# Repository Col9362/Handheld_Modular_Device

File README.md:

# Handheld Modular Device

A handheld built around hot-swappable control modules. Modules attach to the base unit
through an 8-pin pogo connector, and the base detects which module is attached
over I2C plus a resistor-divider ID line.

More details and photos: https://colezuckerman.com/projects/modular-handheld/

## Repository layout

| Folder | Contents |
|---|---|
| `base/` | KiCad project for the base unit (Raspberry Pi Pico, display connector, buzzers, pogo connector) |
| `base/gerbers/` | Manufacturing files for the base unit PCB |
| `base/backup-2026-06-27/` | Earlier snapshot of the base unit KiCad project |
| `gaming-module/` | Gaming controller module (MCP23017 buttons, joystick, haptics) |
| `gaming-module/gerbers/` | Manufacturing files for the gaming module PCB |
| `firmware/` | MicroPython code that runs on the base unit's Pico |

### Gaming module note

The original KiCad project files for the gaming module were lost. The Gerbers in
`gaming-module/gerbers/` are the exact files the board was manufactured from.
`schematic.png` is a screenshot of the original schematic, and `preview-top.png` /
`preview-bottom.png` are renders of the board.

## Firmware

Copy everything in `firmware/` to the root of the Pico's filesystem (for example with
Thonny). `main.py` runs at boot.

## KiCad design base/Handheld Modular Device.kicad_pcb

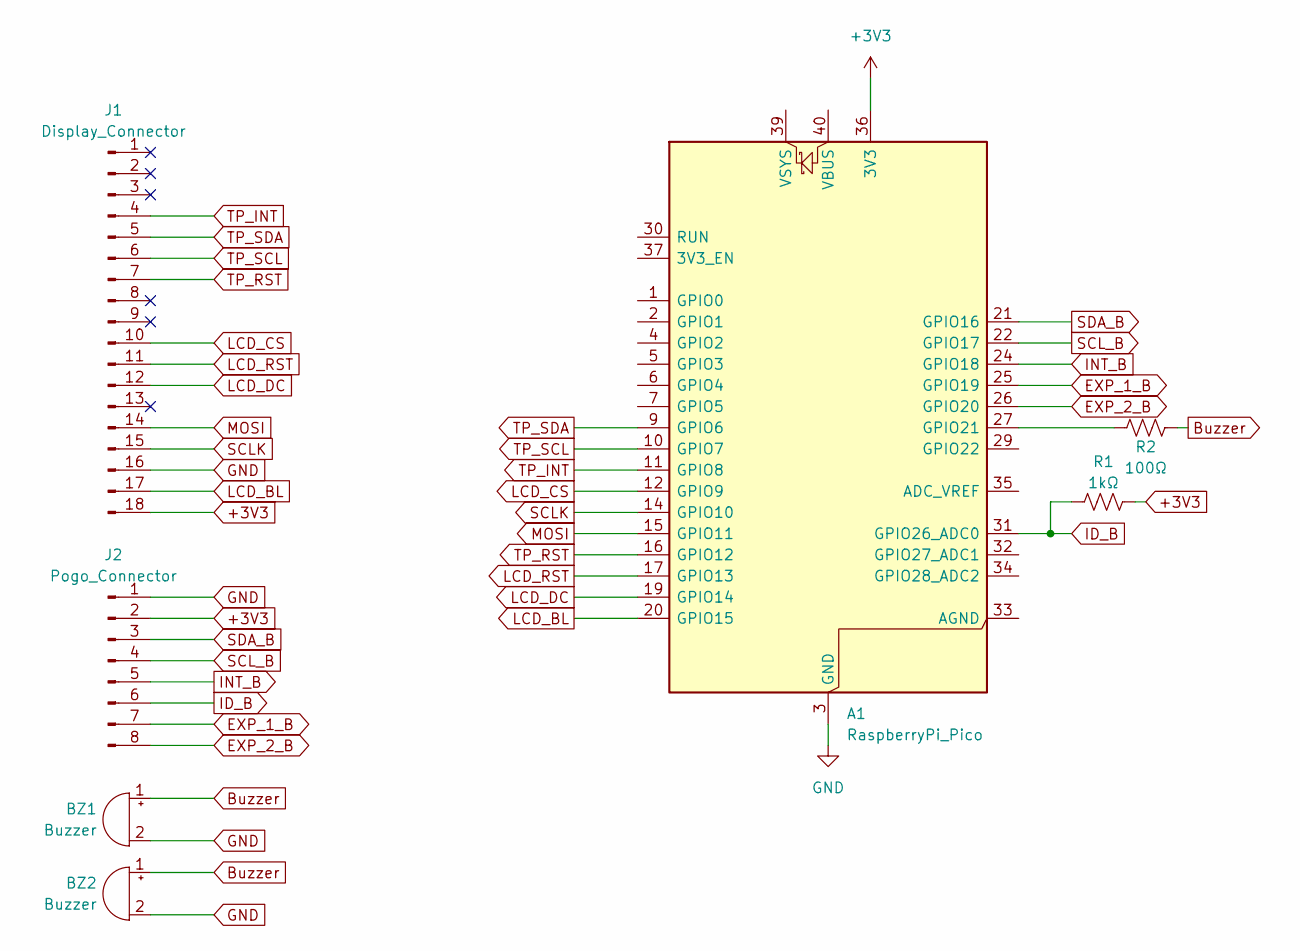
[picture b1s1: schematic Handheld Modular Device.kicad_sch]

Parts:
A1: RaspberryPi_Pico; RaspberryPi_Pico_Common_Unspecified
BZ1, BZ2: Buzzer; Buzzer_12x9.5RM7.6
J1: Display_Connector; Amphenol_F32R-1A7x1-11018_1x18-1MP_P0.5mm_Horizontal
J2: Pogo_Connector; PinHeader_1x08_P2.54mm_Vertical
R1: 1kΩ; R_Axial_DIN0207_L6.3mm_D2.5mm_P10.16mm_Horizontal
R2: 100Ω; R_Axial_DIN0207_L6.3mm_D2.5mm_P10.16mm_Horizontal

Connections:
+3V3: A1.36 (3V3), J1.18, J2.2, R1.2
Buzzer: BZ1.1 (+), BZ2.1 (+), R2.2
EXP_1_B: A1.25 (GPIO19), J2.7
EXP_2_B: A1.26 (GPIO20), J2.8
GND: A1.3 (GND), A1.8 (GND), A1.13 (GND), A1.18 (GND), A1.23 (GND), A1.28 (GND), A1.38 (GND), BZ1.2 (-), BZ2.2 (-), J1.16, J2.1
ID_B: A1.31 (GPIO26_ADC0), J2.6, R1.1
INT_B: A1.24 (GPIO18), J2.5
LCD_BL: A1.20 (GPIO15), J1.17
LCD_CS: A1.12 (GPIO9), J1.10
LCD_DC: A1.19 (GPIO14), J1.12
LCD_RST: A1.17 (GPIO13), J1.11
MOSI: A1.15 (GPIO11), J1.14
unnamed: A1.27 (GPIO21), R2.1
SCLK: A1.14 (GPIO10), J1.15
SCL_B: A1.22 (GPIO17), J2.4
SDA_B: A1.21 (GPIO16), J2.3
TP_INT: A1.11 (GPIO8), J1.4
TP_RST: A1.16 (GPIO12), J1.7
TP_SCL: A1.10 (GPIO7), J1.6
TP_SDA: A1.9 (GPIO6), J1.5

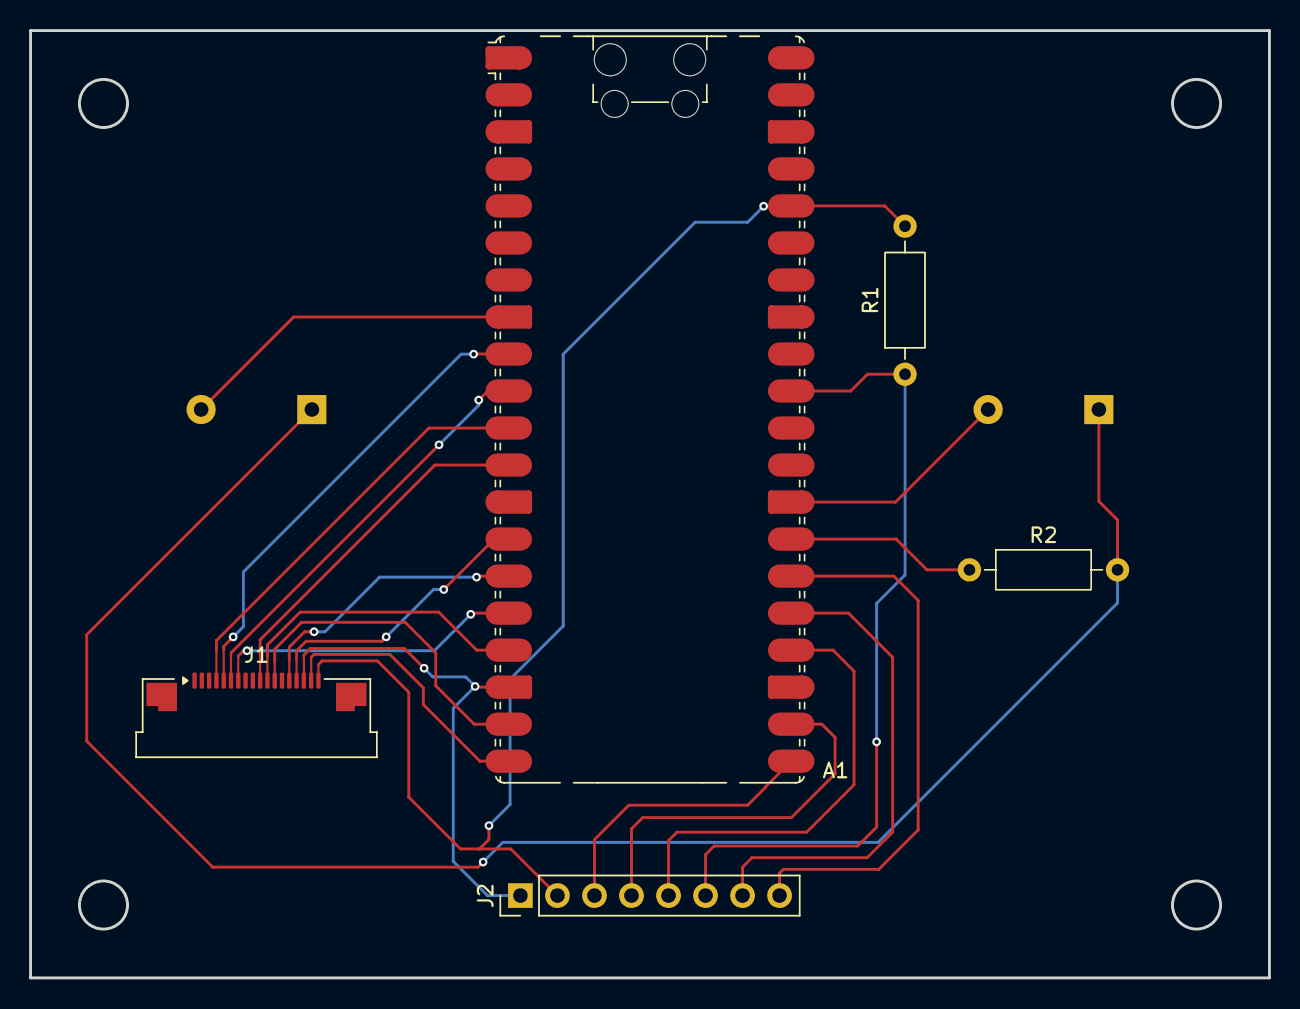
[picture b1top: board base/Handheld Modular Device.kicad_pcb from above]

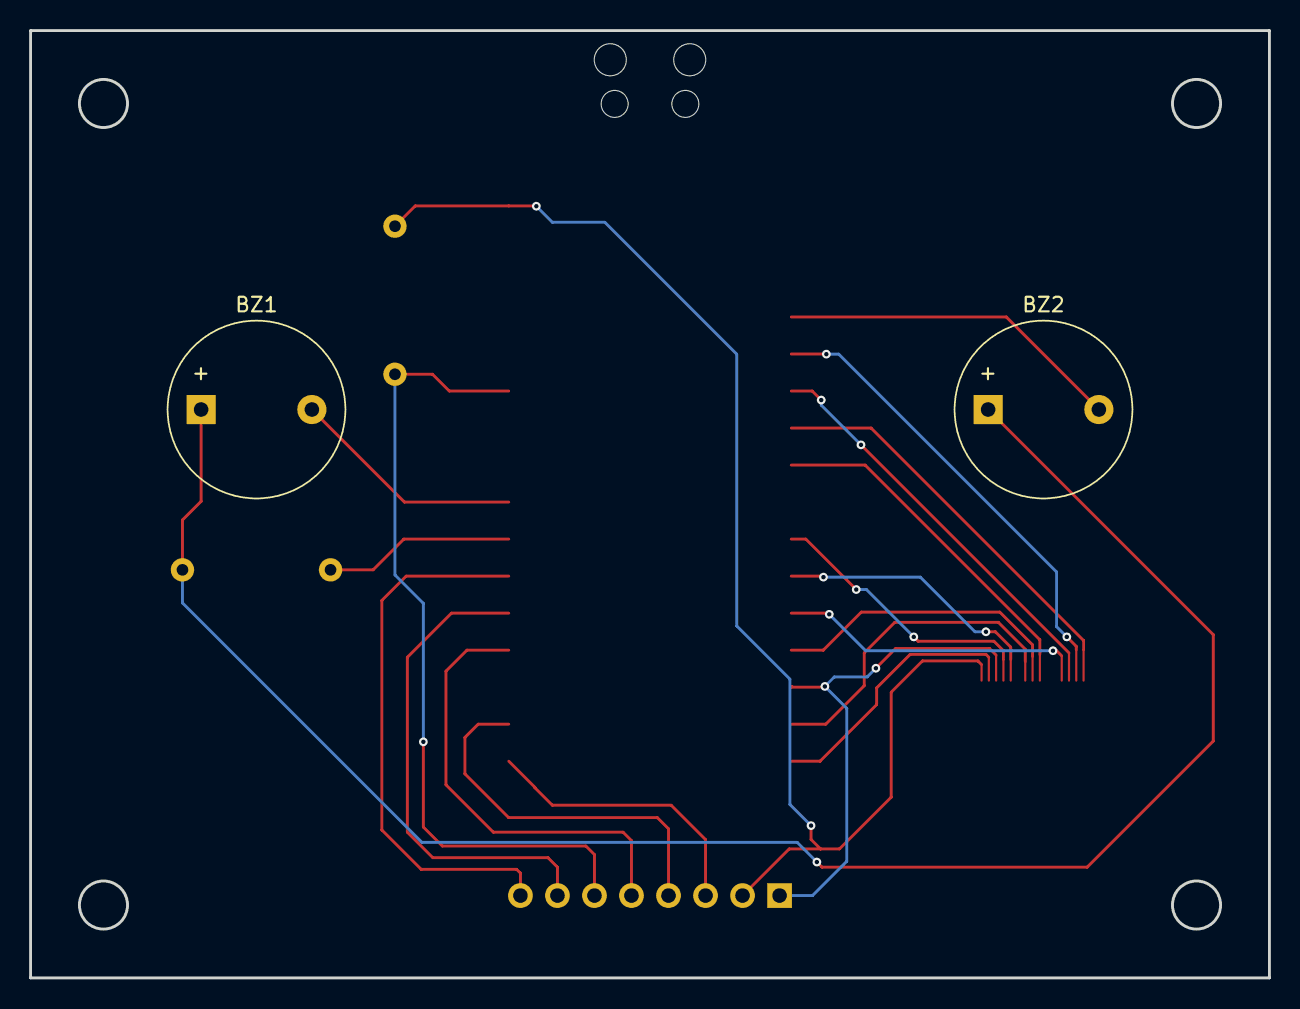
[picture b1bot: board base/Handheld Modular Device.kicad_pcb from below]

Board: 2 copper layers, 85.0 x 65.0 mm, 7 parts (2 on the bottom side), 20 nets.

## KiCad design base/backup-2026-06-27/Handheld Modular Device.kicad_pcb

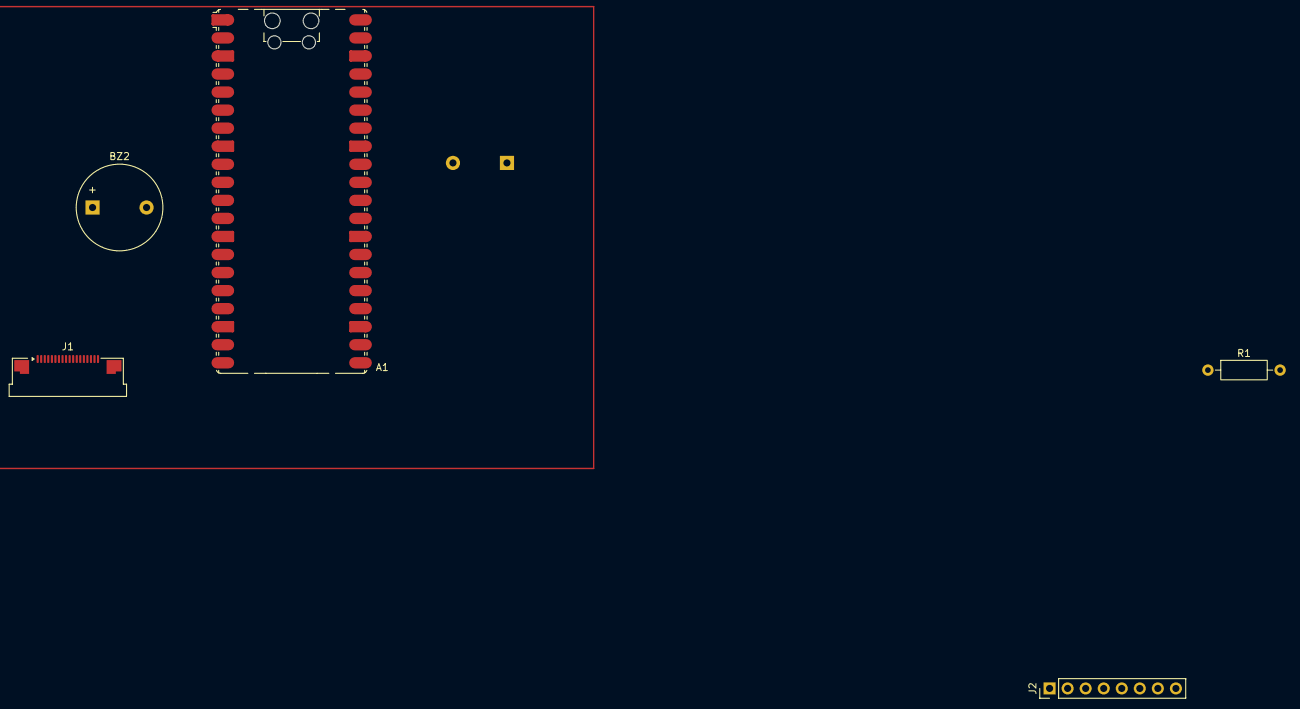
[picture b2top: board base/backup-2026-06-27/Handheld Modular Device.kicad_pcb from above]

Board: 2 copper layers, 6 parts (1 on the bottom side), 19 nets, no tracks yet.

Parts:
A1: RaspberryPi_Pico; RaspberryPi_Pico_Common_Unspecified
BZ1, BZ2: Buzzer; Buzzer_12x9.5RM7.6
J1: Display_Connector; Amphenol_F32R-1A7x1-11018_1x18-1MP_P0.5mm_Horizontal
J2: Pogo_Connector; PinHeader_1x08_P2.54mm_Vertical
R1: R_US; R_Axial_DIN0207_L6.3mm_D2.5mm_P10.16mm_Horizontal

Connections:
+3V3: A1.36 (3V3), J1.1, J2.2, R1.2
Buzzer: A1.27 (GPIO21), BZ1.1 (+), BZ2.1 (+)
EXP_1_B: A1.25 (GPIO19), J2.7
EXP_2_B: A1.26 (GPIO20), J2.8
GND: A1.3 (GND), A1.8 (GND), A1.13 (GND), A1.18 (GND), A1.23 (GND), A1.28 (GND), A1.38 (GND), BZ1.2 (-), BZ2.2 (-), J1.3, J2.1
ID_B: A1.31 (GPIO26_ADC0), J2.6, R1.1
INT_B: A1.24 (GPIO18), J2.5
LCD_BL: A1.20 (GPIO15), J1.2
LCD_CS: A1.12 (GPIO9), J1.9
LCD_DC: A1.19 (GPIO14), J1.7
LCD_RST: A1.17 (GPIO13), J1.8
MOSI: A1.15 (GPIO11), J1.5
SCLK: A1.14 (GPIO10), J1.4
SCL_B: A1.22 (GPIO17), J2.4
SDA_B: A1.21 (GPIO16), J2.3
TP_INT: A1.11 (GPIO8), J1.15
TP_RST: A1.16 (GPIO12), J1.12
TP_SCL: A1.10 (GPIO7), J1.13
TP_SDA: A1.9 (GPIO6), J1.14
